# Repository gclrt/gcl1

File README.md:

Garbage Collection Module 1

Run compme.tcl from within Modelsim.

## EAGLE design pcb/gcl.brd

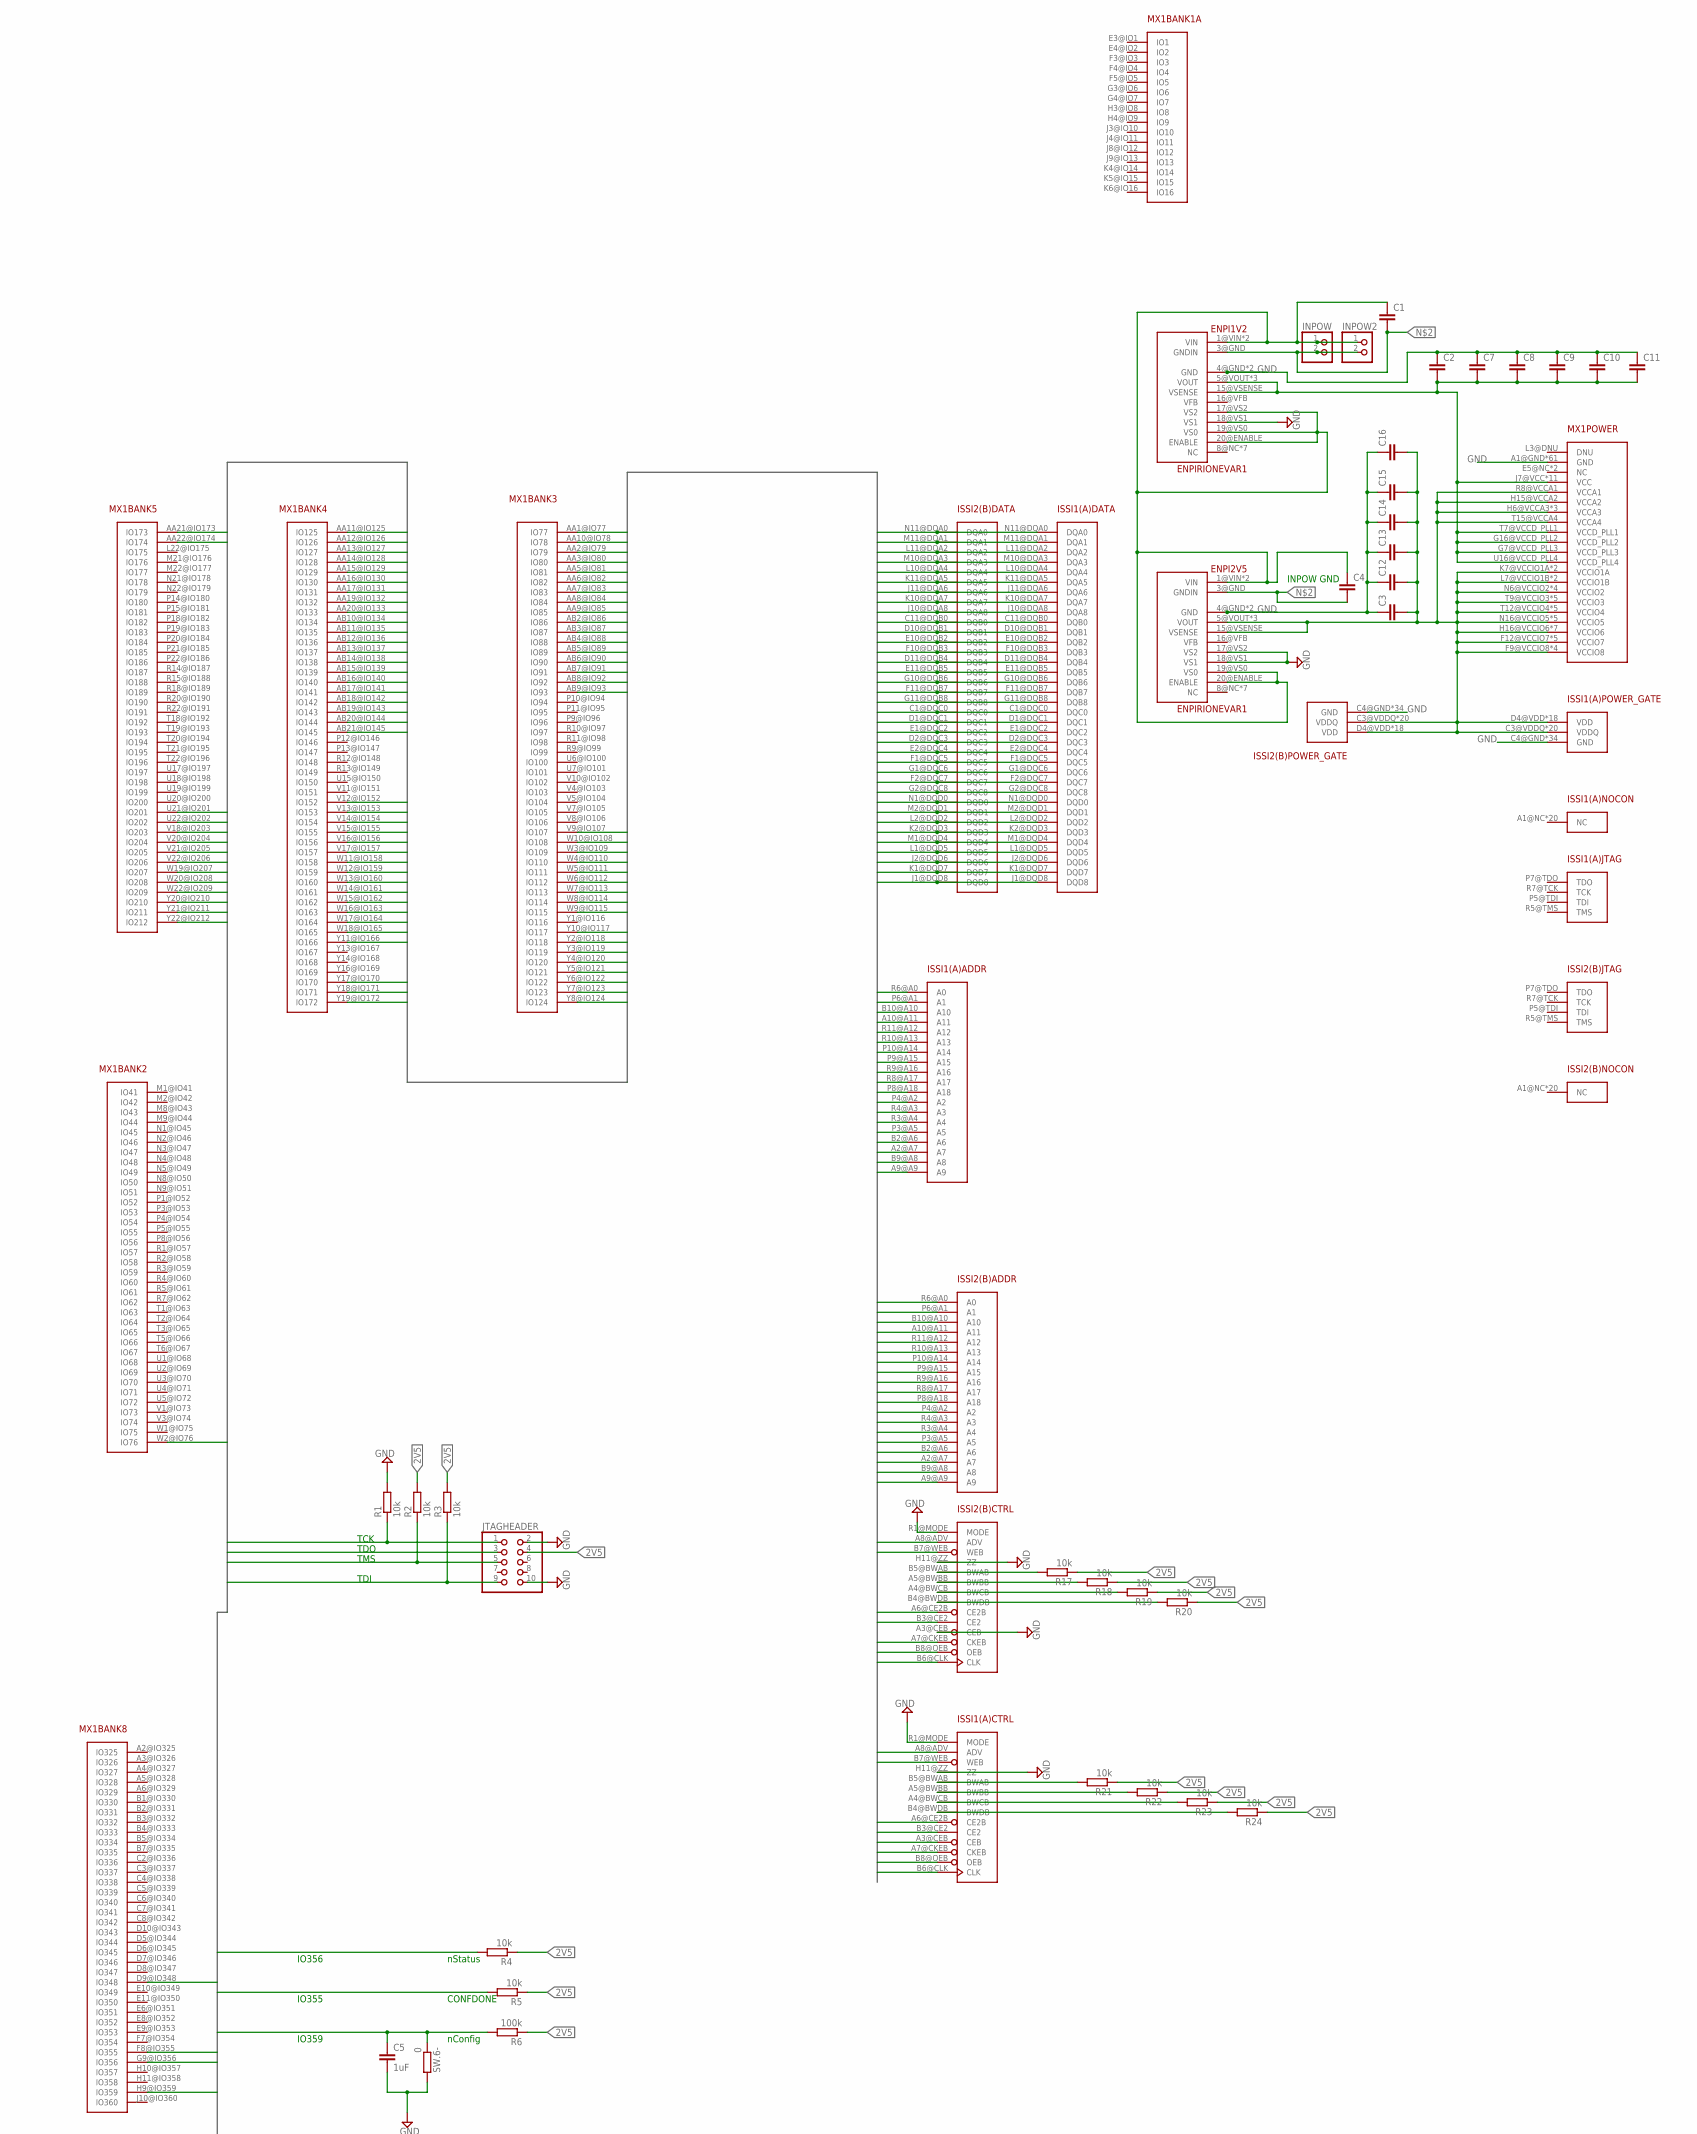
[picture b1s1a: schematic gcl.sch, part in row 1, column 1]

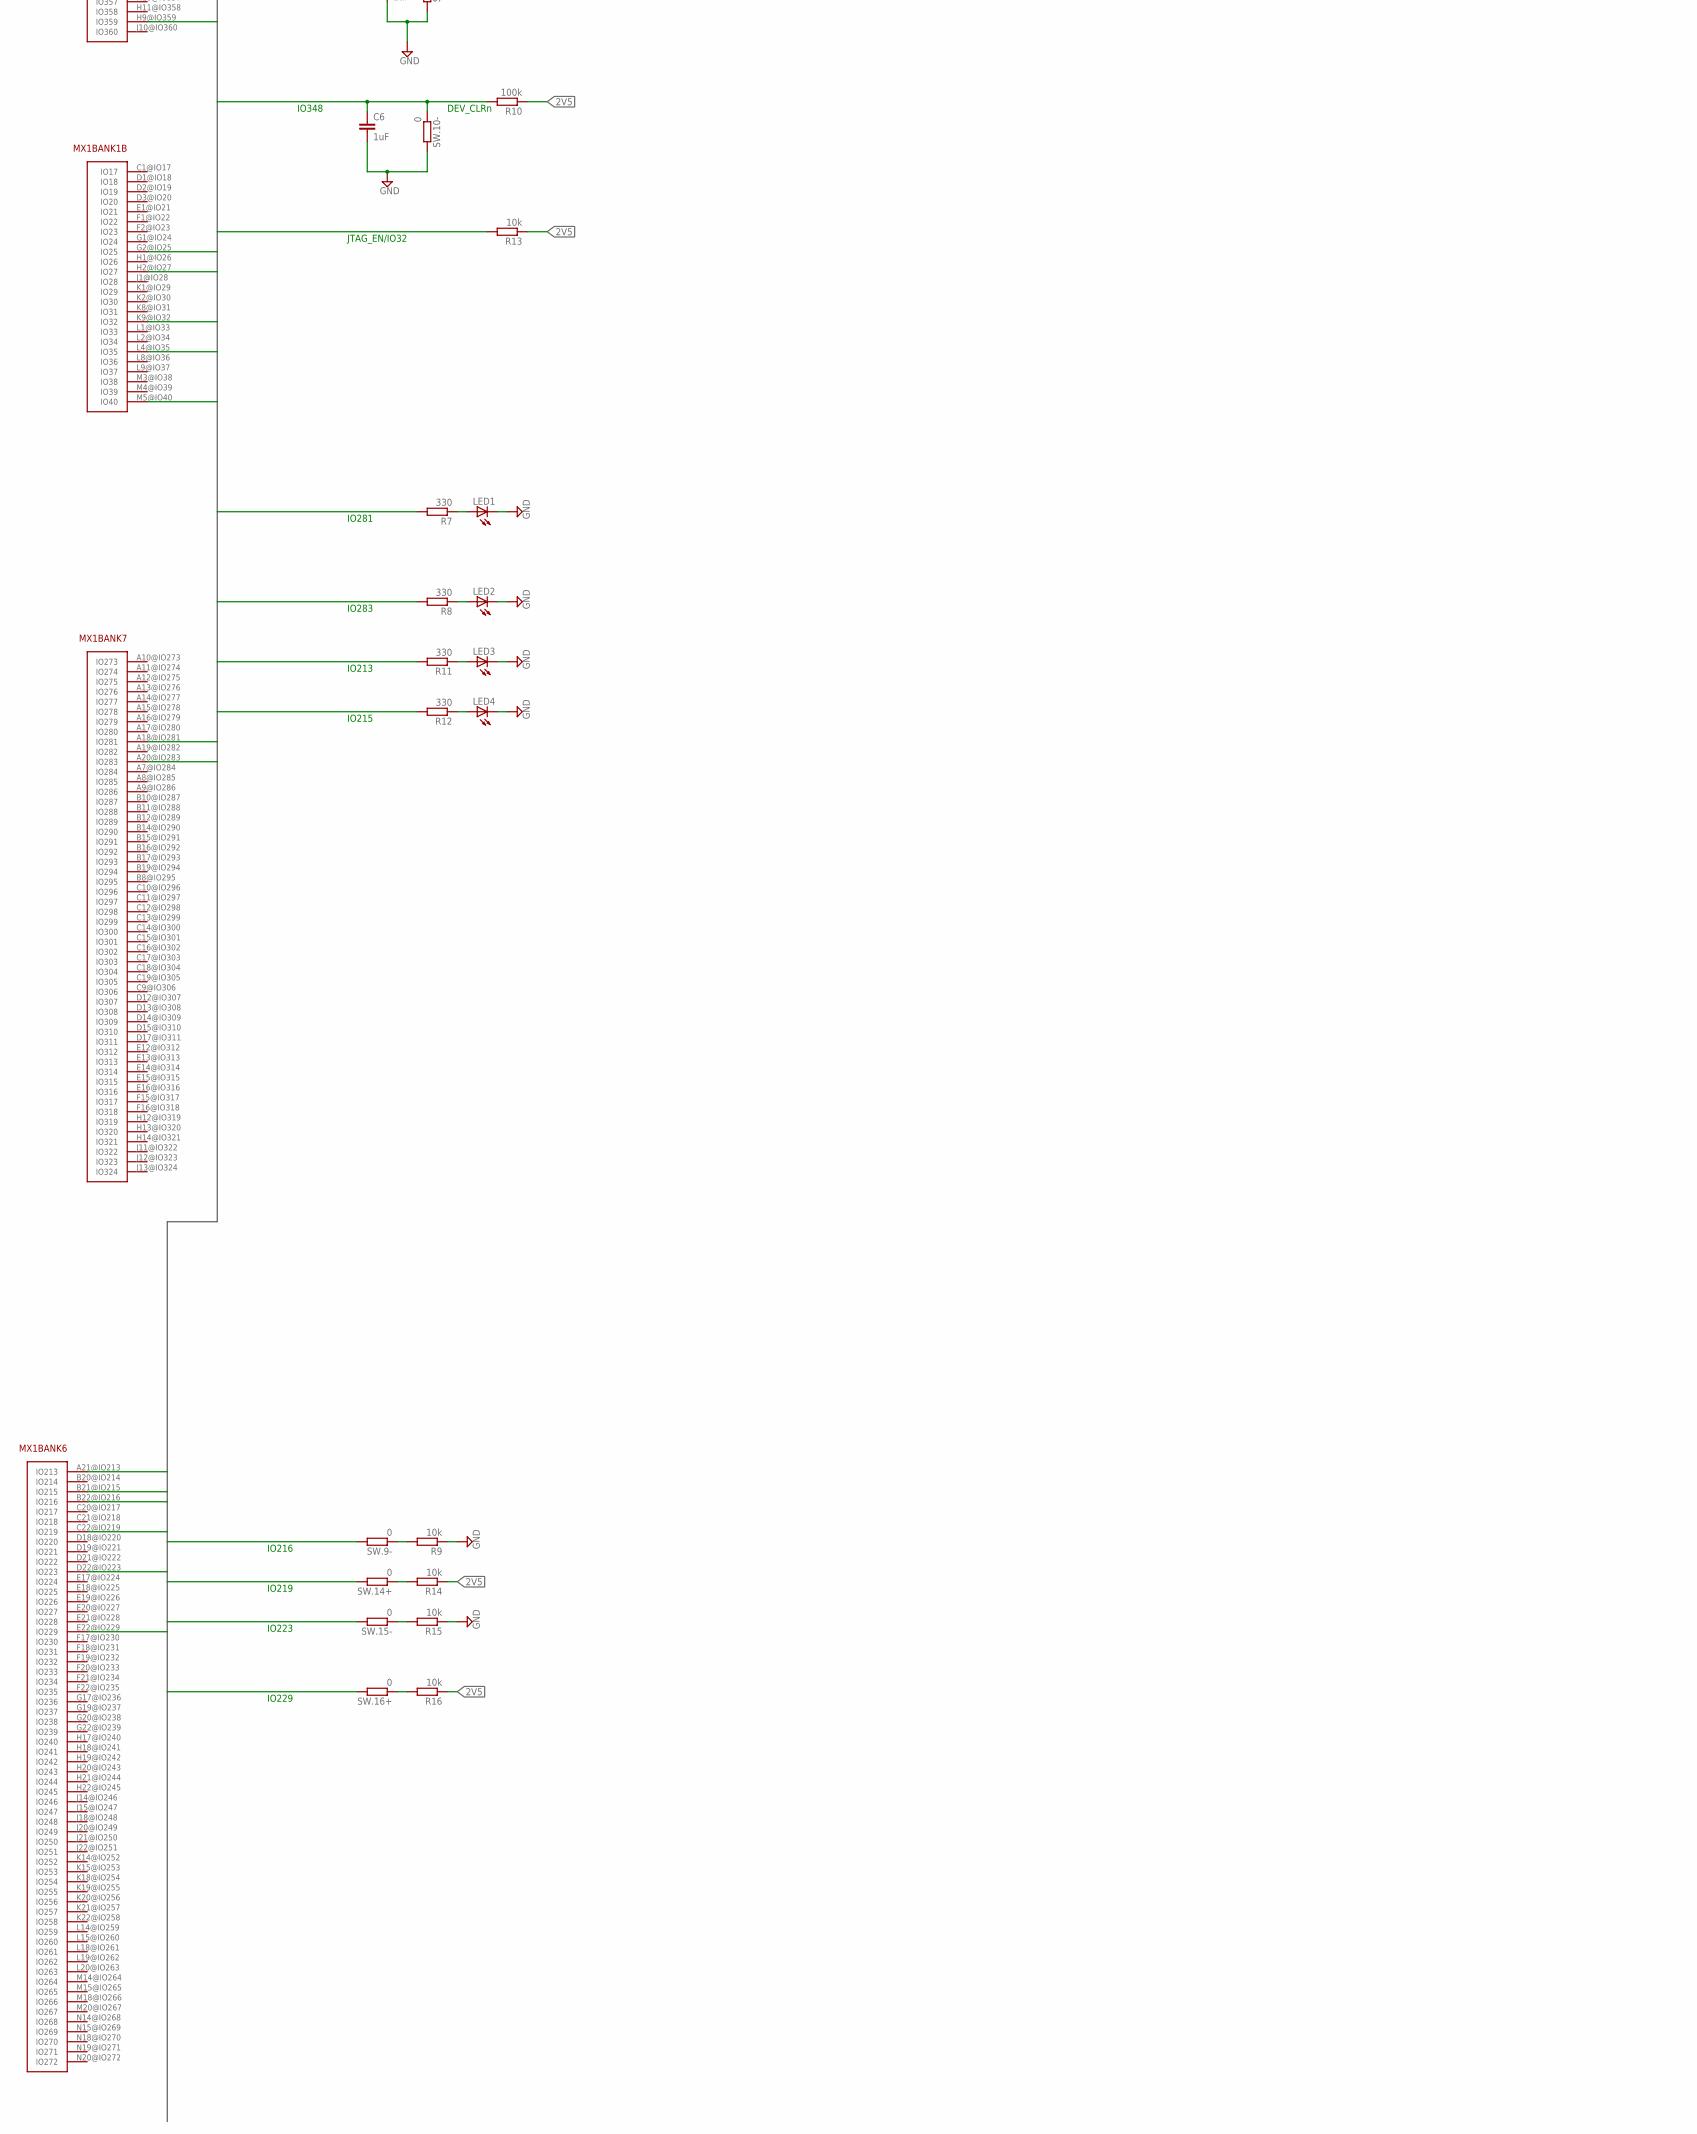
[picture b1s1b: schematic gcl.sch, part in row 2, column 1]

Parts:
C1, C2, C3, C4, C7, C8, C9, C10, C11, C12, C13, C14, C15, C16: C-EUC0805; C0805
C5, C6: 1uF; C0805
ENPI1V2, ENPI2V5: ENPIRIONEVAR1; EPAC
INPOW, INPOW2: PINHD-1X2; 1X02
ISSI1(A), ISSI2(B): ISSIDEVISSIVAR; ISSI
JTAGHEADER: PINHD-2X5; 2X05
LED1, LED2, LED3, LED4: LEDSML0805; SML0805
MX1: MXMXDEVICE; MXPAC
R1, R2, R3, R4, R5, R9, R13, R14, R15, R16, R17, R18, R19, R20, R21, R22, R23, R24: 10k; M0805
R6, R10: 100k; M0805
R7, R8, R11, R12: 330; M0805
SW.6-, SW.9-, SW.10-, SW.14+, SW.15-, SW.16+: 0; M0805

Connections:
1V2: C2.2, C7.2, C8.2, C9.2, C10.2, C11.2, ENPI1V2.5@VOUT (VOUT), ENPI1V2.6@VOUT (VOUT), ENPI1V2.7@VOUT (VOUT), ENPI1V2.15@VSENSE (VSENSE), MX1.G7@VCCD_PLL3 (VCCD_PLL3), MX1.G16@VCCD_PLL2 (VCCD_PLL2), MX1.J7@VCC (VCC), MX1.K11@VCC (VCC), MX1.K13@VCC (VCC), MX1.L10@VCC (VCC), MX1.L11@VCC (VCC), MX1.L12@VCC (VCC), MX1.M11@VCC (VCC), MX1.M12@VCC (VCC), MX1.M13@VCC (VCC), MX1.N10@VCC (VCC), MX1.N12@VCC (VCC), MX1.T7@VCCD_PLL1 (VCCD_PLL1), MX1.U16@VCCD_PLL4 (VCCD_PLL4)
2V5: C3.2, C12.2, C13.2, C14.2, C15.2, C16.2, ENPI2V5.5@VOUT (VOUT), ENPI2V5.6@VOUT (VOUT), ENPI2V5.7@VOUT (VOUT), ENPI2V5.15@VSENSE (VSENSE), ISSI1(A).C3@VDDQ (VDDQ), ISSI1(A).C9@VDDQ (VDDQ), ISSI1(A).D3@VDDQ (VDDQ), ISSI1(A).D4@VDD (VDD), ISSI1(A).D8@VDD (VDD), ISSI1(A).D9@VDDQ (VDDQ), ISSI1(A).E3@VDDQ (VDDQ), ISSI1(A).E4@VDD (VDD), ISSI1(A).E8@VDD (VDD), ISSI1(A).E9@VDDQ (VDDQ), ISSI1(A).F3@VDDQ (VDDQ), ISSI1(A).F4@VDD (VDD), ISSI1(A).F8@VDD (VDD), ISSI1(A).F9@VDDQ (VDDQ), ISSI1(A).G3@VDDQ (VDDQ), ISSI1(A).G4@VDD (VDD), ISSI1(A).G8@VDD (VDD), ISSI1(A).G9@VDDQ (VDDQ), ISSI1(A).H4@VDD (VDD), ISSI1(A).H8@VDD (VDD), ISSI1(A).J3@VDDQ (VDDQ), ISSI1(A).J4@VDD (VDD), ISSI1(A).J8@VDD (VDD), ISSI1(A).J9@VDDQ (VDDQ), ISSI1(A).K3@VDDQ (VDDQ), ISSI1(A).K4@VDD (VDD), ISSI1(A).K8@VDD (VDD), ISSI1(A).K9@VDDQ (VDDQ), ISSI1(A).L3@VDDQ (VDDQ), ISSI1(A).L4@VDD (VDD), ISSI1(A).L8@VDD (VDD), ISSI1(A).L9@VDDQ (VDDQ), ISSI1(A).M3@VDDQ (VDDQ), ISSI1(A).M4@VDD (VDD), ISSI1(A).M8@VDD (VDD), ISSI1(A).M9@VDDQ (VDDQ), ISSI1(A).N3@VDDQ (VDDQ), ISSI1(A).N9@VDDQ (VDDQ), ISSI2(B).C3@VDDQ (VDDQ), ISSI2(B).C9@VDDQ (VDDQ), ISSI2(B).D3@VDDQ (VDDQ), ISSI2(B).D4@VDD (VDD), ISSI2(B).D8@VDD (VDD), ISSI2(B).D9@VDDQ (VDDQ), ISSI2(B).E3@VDDQ (VDDQ), ISSI2(B).E4@VDD (VDD), ISSI2(B).E8@VDD (VDD), ISSI2(B).E9@VDDQ (VDDQ), ISSI2(B).F3@VDDQ (VDDQ), ISSI2(B).F4@VDD (VDD), ISSI2(B).F8@VDD (VDD), ISSI2(B).F9@VDDQ (VDDQ), ISSI2(B).G3@VDDQ (VDDQ), ISSI2(B).G4@VDD (VDD), ISSI2(B).G8@VDD (VDD), ISSI2(B).G9@VDDQ (VDDQ), ISSI2(B).H4@VDD (VDD), ISSI2(B).H8@VDD (VDD), ISSI2(B).J3@VDDQ (VDDQ), ISSI2(B).J4@VDD (VDD), ISSI2(B).J8@VDD (VDD), ISSI2(B).J9@VDDQ (VDDQ), ISSI2(B).K3@VDDQ (VDDQ), ISSI2(B).K4@VDD (VDD), ISSI2(B).K8@VDD (VDD), ISSI2(B).K9@VDDQ (VDDQ), ISSI2(B).L3@VDDQ (VDDQ), ISSI2(B).L4@VDD (VDD), ISSI2(B).L8@VDD (VDD), ISSI2(B).L9@VDDQ (VDDQ), ISSI2(B).M3@VDDQ (VDDQ), ISSI2(B).M4@VDD (VDD), ISSI2(B).M8@VDD (VDD), ISSI2(B).M9@VDDQ (VDDQ), ISSI2(B).N3@VDDQ (VDDQ), ISSI2(B).N9@VDDQ (VDDQ), JTAGHEADER.4, MX1.F9@VCCIO8 (VCCIO8), MX1.F11@VCCIO8 (VCCIO8), MX1.F12@VCCIO7 (VCCIO7), MX1.F14@VCCIO7 (VCCIO7), MX1.G10@VCCIO8 (VCCIO8), MX1.G11@VCCIO8 (VCCIO8), MX1.G12@VCCIO7 (VCCIO7), MX1.G13@VCCIO7 (VCCIO7), MX1.G14@VCCIO7 (VCCIO7), MX1.H6@VCCA3 (VCCA3), MX1.H7@VCCA3 (VCCA3), MX1.H8@VCCA3 (VCCA3), MX1.H15@VCCA2 (VCCA2), MX1.H16@VCCIO6 (VCCIO6), MX1.J17@VCCIO6 (VCCIO6), MX1.K7@VCCIO1A (VCCIO1A), MX1.K16@VCCIO6 (VCCIO6), MX1.K17@VCCIO6 (VCCIO6), MX1.L6@VCCIO1A (VCCIO1A), MX1.L7@VCCIO1B (VCCIO1B), MX1.L16@VCCIO6 (VCCIO6), MX1.M6@VCCIO1B (VCCIO1B), MX1.M17@VCCIO6 (VCCIO6), MX1.N6@VCCIO2 (VCCIO2), MX1.N7@VCCIO2 (VCCIO2), MX1.N16@VCCIO5 (VCCIO5), MX1.N17@VCCIO6 (VCCIO6), MX1.P7@VCCIO2 (VCCIO2), MX1.P16@VCCIO5 (VCCIO5), MX1.R6@VCCIO2 (VCCIO2), MX1.R8@VCCA1 (VCCA1), MX1.R16@VCCIO5 (VCCIO5), MX1.R17@VCCIO5 (VCCIO5), MX1.T9@VCCIO3 (VCCIO3), MX1.T10@VCCIO3 (VCCIO3), MX1.T11@VCCIO3 (VCCIO3), MX1.T12@VCCIO4 (VCCIO4), MX1.T13@VCCIO4 (VCCIO4), MX1.T15@VCCA4 (VCCA4), MX1.T17@VCCIO5 (VCCIO5), MX1.U8@VCCIO3 (VCCIO3), MX1.U9@VCCIO3 (VCCIO3), MX1.U11@VCCIO4 (VCCIO4), MX1.U12@VCCIO4 (VCCIO4), MX1.U14@VCCIO4 (VCCIO4), R2.2, R3.2, R4.1, R5.1, R6.1, R10.1, R13.1, R14.1, R16.1, R17.1, R18.1, R19.1, R20.1, R21.1, R22.1, R23.1, R24.1
GND: C2.1, C3.1, C5.2, C6.2, C7.1, C8.1, C9.1, C10.1, C11.1, C12.1, C13.1, C14.1, C15.1, C16.1, ENPI1V2.4@GND (GND), ENPI1V2.18@VS1 (VS1), ENPI1V2.21@GND (GND), ENPI2V5.4@GND (GND), ENPI2V5.17@VS2 (VS2), ENPI2V5.18@VS1 (VS1), ENPI2V5.21@GND (GND), ISSI1(A).C4@GND (GND), ISSI1(A).C5@GND (GND), ISSI1(A).C6@GND (GND), ISSI1(A).C7@GND (GND), ISSI1(A).C8@GND (GND), ISSI1(A).D5@GND (GND), ISSI1(A).D6@GND (GND), ISSI1(A).D7@GND (GND), ISSI1(A).E5@GND (GND), ISSI1(A).E6@GND (GND), ISSI1(A).E7@GND (GND), ISSI1(A).F5@GND (GND), ISSI1(A).F6@GND (GND), ISSI1(A).F7@GND (GND), ISSI1(A).G5@GND (GND), ISSI1(A).G6@GND (GND), ISSI1(A).G7@GND (GND), ISSI1(A).H5@GND (GND), ISSI1(A).H6@GND (GND), ISSI1(A).H7@GND (GND), ISSI1(A).H11@ZZ (ZZ), ISSI1(A).J5@GND (GND), ISSI1(A).J6@GND (GND), ISSI1(A).J7@GND (GND), ISSI1(A).K5@GND (GND), ISSI1(A).K6@GND (GND), ISSI1(A).K7@GND (GND), ISSI1(A).L5@GND (GND), ISSI1(A).L6@GND (GND), ISSI1(A).L7@GND (GND), ISSI1(A).M5@GND (GND), ISSI1(A).M6@GND (GND), ISSI1(A).M7@GND (GND), ISSI1(A).N4@GND (GND), ISSI1(A).N8@GND (GND), ISSI1(A).R1@MODE (MODE), ISSI2(B).A3@CEB (CEB), ISSI2(B).C4@GND (GND), ISSI2(B).C5@GND (GND), ISSI2(B).C6@GND (GND), ISSI2(B).C7@GND (GND), ISSI2(B).C8@GND (GND), ISSI2(B).D5@GND (GND), ISSI2(B).D6@GND (GND), ISSI2(B).D7@GND (GND), ISSI2(B).E5@GND (GND), ISSI2(B).E6@GND (GND), ISSI2(B).E7@GND (GND), ISSI2(B).F5@GND (GND), ISSI2(B).F6@GND (GND), ISSI2(B).F7@GND (GND), ISSI2(B).G5@GND (GND), ISSI2(B).G6@GND (GND), ISSI2(B).G7@GND (GND), ISSI2(B).H5@GND (GND), ISSI2(B).H6@GND (GND), ISSI2(B).H7@GND (GND), ISSI2(B).H11@ZZ (ZZ), ISSI2(B).J5@GND (GND), ISSI2(B).J6@GND (GND), ISSI2(B).J7@GND (GND), ISSI2(B).K5@GND (GND), ISSI2(B).K6@GND (GND), ISSI2(B).K7@GND (GND), ISSI2(B).L5@GND (GND), ISSI2(B).L6@GND (GND), ISSI2(B).L7@GND (GND), ISSI2(B).M5@GND (GND), ISSI2(B).M6@GND (GND), ISSI2(B).M7@GND (GND), ISSI2(B).N4@GND (GND), ISSI2(B).N8@GND (GND), ISSI2(B).R1@MODE (MODE), JTAGHEADER.2, JTAGHEADER.10, LED1.C, LED2.C, LED3.C, LED4.C, MX1.A1@GND (GND), MX1.A22@GND (GND), MX1.AA4@GND (GND), MX1.AA18@GND (GND), MX1.AB1@GND (GND), MX1.AB22@GND (GND), MX1.B6@GND (GND), MX1.B9@GND (GND), MX1.B13@GND (GND), MX1.B18@GND (GND), MX1.D4@GND (GND), MX1.D11@GND (GND), MX1.D16@GND (GND), MX1.D20@GND (GND), MX1.E2@GND (GND), MX1.E7@GND (GND), MX1.F10@GND (GND), MX1.F13@GND (GND), MX1.G5@GND (GND), MX1.G6@GND (GND), MX1.G8@GND (GND), MX1.G15@GND (GND), MX1.G18@GND (GND), MX1.G21@GND (GND), MX1.H5@GND (GND), MX1.J2@GND (GND), MX1.J5@GND (GND), MX1.J6@GND (GND), MX1.J16@GND (GND), MX1.J19@GND (GND), MX1.K3@GND (GND), MX1.K10@GND (GND), MX1.K12@GND (GND), MX1.L5@GND (GND), MX1.L13@GND (GND), MX1.L17@GND (GND), MX1.L21@GND (GND), MX1.M7@GND (GND), MX1.M10@GND (GND), MX1.M16@GND (GND), MX1.M19@GND (GND), MX1.N11@GND (GND), MX1.N13@GND (GND), MX1.P2@GND (GND), MX1.P6@GND (GND), MX1.P17@GND (GND), MX1.R19@GND (GND), MX1.R21@GND (GND), MX1.T4@GND (GND), MX1.T8@GND (GND), MX1.T14@GND (GND), MX1.T16@GND (GND), MX1.U10@GND (GND), MX1.U13@GND (GND), MX1.V2@GND (GND), MX1.V6@GND (GND), MX1.V19@GND (GND), MX1.W21@GND (GND), MX1.Y9@GND (GND), MX1.Y12@GND (GND), MX1.Y15@GND (GND), R1.2, R9.1, R15.1, SW.6-.2, SW.10-.2
IO25: JTAGHEADER.1, MX1.G2@IO25 (IO25), R1.1
IO27: JTAGHEADER.5, MX1.H2@IO27 (IO27), R2.1
IO32: MX1.K9@IO32 (IO32), R13.2
IO35: JTAGHEADER.9, MX1.L4@IO35 (IO35), R3.1
IO40: JTAGHEADER.3, MX1.M5@IO40 (IO40)
IO76: ISSI2(B).A7@CKEB (CKEB), MX1.W2@IO76 (IO76)
IO77: ISSI2(B).B7@WEB (WEB), MX1.AA1@IO77 (IO77)
IO78: ISSI1(A).E2@DQC4 (DQC4), ISSI2(B).E2@DQC4 (DQC4), MX1.AA10@IO78 (IO78)
IO79: ISSI1(A).A3@CEB (CEB), MX1.AA2@IO79 (IO79)
IO80: ISSI1(A).A10@A11 (A11), MX1.AA3@IO80 (IO80)
IO81: ISSI1(A).B2@A6 (A6), MX1.AA5@IO81 (IO81)
IO82: ISSI1(A).B8@OEB (OEB), MX1.AA6@IO82 (IO82)
IO83: ISSI2(B).B10@A10 (A10), MX1.AA7@IO83 (IO83)
IO84: ISSI2(B).B2@A6 (A6), MX1.AA8@IO84 (IO84)
IO85: ISSI1(A).D2@DQC3 (DQC3), ISSI2(B).D2@DQC3 (DQC3), MX1.AA9@IO85 (IO85)
IO86: ISSI1(A).A2@A7 (A7), MX1.AB2@IO86 (IO86)
IO87: ISSI1(A).A7@CKEB (CKEB), MX1.AB3@IO87 (IO87)
IO88: ISSI2(B).B8@OEB (OEB), MX1.AB4@IO88 (IO88)
IO89: ISSI1(A).A6@CE2B (CE2B), MX1.AB5@IO89 (IO89)
IO90: ISSI1(A).B7@WEB (WEB), MX1.AB6@IO90 (IO90)
IO91: ISSI2(B).A10@A11 (A11), MX1.AB7@IO91 (IO91)
IO92: ISSI1(A).C1@DQC0 (DQC0), ISSI2(B).C1@DQC0 (DQC0), MX1.AB8@IO92 (IO92)
IO93: ISSI1(A).D1@DQC1 (DQC1), ISSI2(B).D1@DQC1 (DQC1), MX1.AB9@IO93 (IO93)
IO107: ISSI1(A).D11@DQB4 (DQB4), ISSI2(B).D11@DQB4 (DQB4), MX1.V9@IO107 (IO107)
IO108: ISSI1(A).E11@DQB5 (DQB5), ISSI2(B).E11@DQB5 (DQB5), MX1.W10@IO108 (IO108)
IO109: ISSI1(A).A8@ADV (ADV), MX1.W3@IO109 (IO109)
IO110: ISSI2(B).A6@CE2B (CE2B), MX1.W4@IO110 (IO110)
IO111: ISSI1(A).B6@CLK (CLK), ISSI2(B).B6@CLK (CLK), MX1.W5@IO111 (IO111)
IO112: ISSI1(A).B10@A10 (A10), MX1.W6@IO112 (IO112)
IO113: ISSI2(B).B9@A8 (A8), MX1.W7@IO113 (IO113)
IO114: ISSI1(A).C11@DQB0 (DQB0), ISSI2(B).C11@DQB0 (DQB0), MX1.W8@IO114 (IO114)
IO115: ISSI1(A).D10@DQB1 (DQB1), ISSI2(B).D10@DQB1 (DQB1), MX1.W9@IO115 (IO115)
IO117: ISSI1(A).E10@DQB2 (DQB2), ISSI2(B).E10@DQB2 (DQB2), MX1.Y10@IO117 (IO117)
IO118: ISSI2(B).A8@ADV (ADV), MX1.Y2@IO118 (IO118)
IO119: ISSI1(A).A9@A9 (A9), MX1.Y3@IO119 (IO119)
IO120: ISSI2(B).B3@CE2 (CE2), MX1.Y4@IO120 (IO120)
IO121: ISSI1(A).B3@CE2 (CE2), MX1.Y5@IO121 (IO121)
IO122: ISSI1(A).B9@A8 (A8), MX1.Y6@IO122 (IO122)
IO123: ISSI2(B).A9@A9 (A9), MX1.Y7@IO123 (IO123)
IO124: ISSI2(B).A2@A7 (A7), MX1.Y8@IO124 (IO124)
IO125: ISSI1(A).F2@DQC7 (DQC7), ISSI2(B).F2@DQC7 (DQC7), MX1.AA11@IO125 (IO125)
IO126: ISSI1(A).G2@DQC8 (DQC8), ISSI2(B).G2@DQC8 (DQC8), MX1.AA12@IO126 (IO126)
IO127: ISSI1(A).J2@DQD6 (DQD6), ISSI2(B).J2@DQD6 (DQD6), MX1.AA13@IO127 (IO127)
IO128: ISSI1(A).K2@DQD3 (DQD3), ISSI2(B).K2@DQD3 (DQD3), MX1.AA14@IO128 (IO128)
IO129: ISSI1(A).L2@DQD2 (DQD2), ISSI2(B).L2@DQD2 (DQD2), MX1.AA15@IO129 (IO129)
IO130: ISSI1(A).M2@DQD1 (DQD1), ISSI2(B).M2@DQD1 (DQD1), MX1.AA16@IO130 (IO130)
IO131: ISSI2(B).P3@A5 (A5), MX1.AA17@IO131 (IO131)
IO132: ISSI2(B).R10@A13 (A13), MX1.AA19@IO132 (IO132)
IO133: ISSI2(B).R9@A16 (A16), MX1.AA20@IO133 (IO133)
IO134: ISSI1(A).E1@DQC2 (DQC2), ISSI2(B).E1@DQC2 (DQC2), MX1.AB10@IO134 (IO134)
IO135: ISSI1(A).F1@DQC5 (DQC5), ISSI2(B).F1@DQC5 (DQC5), MX1.AB11@IO135 (IO135)
IO136: ISSI1(A).G1@DQC6 (DQC6), ISSI2(B).G1@DQC6 (DQC6), MX1.AB12@IO136 (IO136)
IO137: ISSI1(A).J1@DQD8 (DQD8), ISSI2(B).J1@DQD8 (DQD8), MX1.AB13@IO137 (IO137)
IO138: ISSI1(A).K1@DQD7 (DQD7), ISSI2(B).K1@DQD7 (DQD7), MX1.AB14@IO138 (IO138)
IO139: ISSI1(A).L1@DQD5 (DQD5), ISSI2(B).L1@DQD5 (DQD5), MX1.AB15@IO139 (IO139)
IO140: ISSI1(A).M1@DQD4 (DQD4), ISSI2(B).M1@DQD4 (DQD4), MX1.AB16@IO140 (IO140)
IO141: ISSI1(A).N1@DQD0 (DQD0), ISSI2(B).N1@DQD0 (DQD0), MX1.AB17@IO141 (IO141)
IO142: ISSI2(B).R4@A3 (A3), MX1.AB18@IO142 (IO142)
IO143: ISSI2(B).R11@A12 (A12), MX1.AB19@IO143 (IO143)
IO144: ISSI2(B).R8@A17 (A17), MX1.AB20@IO144 (IO144)
IO145: ISSI1(A).P10@A14 (A14), MX1.AB21@IO145 (IO145)
IO152: ISSI1(A).G11@DQB8 (DQB8), ISSI2(B).G11@DQB8 (DQB8), MX1.V12@IO152 (IO152)
IO153: ISSI1(A).J11@DQA6 (DQA6), ISSI2(B).J11@DQA6 (DQA6), MX1.V13@IO153 (IO153)
IO154: ISSI1(A).K11@DQA5 (DQA5), ISSI2(B).K11@DQA5 (DQA5), MX1.V14@IO154 (IO154)
IO155: ISSI1(A).L11@DQA2 (DQA2), ISSI2(B).L11@DQA2 (DQA2), MX1.V15@IO155 (IO155)
IO156: ISSI1(A).M11@DQA1 (DQA1), ISSI2(B).M11@DQA1 (DQA1), MX1.V16@IO156 (IO156)
IO157: ISSI1(A).N11@DQA0 (DQA0), ISSI2(B).N11@DQA0 (DQA0), MX1.V17@IO157 (IO157)
IO158: ISSI1(A).F11@DQB7 (DQB7), ISSI2(B).F11@DQB7 (DQB7), MX1.W11@IO158 (IO158)
IO159: ISSI1(A).G10@DQB6 (DQB6), ISSI2(B).G10@DQB6 (DQB6), MX1.W12@IO159 (IO159)
IO160: ISSI1(A).J10@DQA8 (DQA8), ISSI2(B).J10@DQA8 (DQA8), MX1.W13@IO160 (IO160)
IO161: ISSI1(A).K10@DQA7 (DQA7), ISSI2(B).K10@DQA7 (DQA7), MX1.W14@IO161 (IO161)
IO162: ISSI1(A).L10@DQA4 (DQA4), ISSI2(B).L10@DQA4 (DQA4), MX1.W15@IO162 (IO162)
IO163: ISSI1(A).M10@DQA3 (DQA3), ISSI2(B).M10@DQA3 (DQA3), MX1.W16@IO163 (IO163)
IO164: ISSI2(B).R3@A4 (A4), MX1.W17@IO164 (IO164)
IO165: ISSI2(B).R6@A0 (A0), MX1.W18@IO165 (IO165)
IO166: ISSI1(A).F10@DQB3 (DQB3), ISSI2(B).F10@DQB3 (DQB3), MX1.Y11@IO166 (IO166)
IO170: ISSI2(B).P4@A2 (A2), MX1.Y17@IO170 (IO170)
IO171: ISSI2(B).P6@A1 (A1), MX1.Y18@IO171 (IO171)
IO172: ISSI2(B).P9@A15 (A15), MX1.Y19@IO172 (IO172)
IO173: ISSI1(A).R11@A12 (A12), MX1.AA21@IO173 (IO173)
IO174: ISSI1(A).P6@A1 (A1), MX1.AA22@IO174 (IO174)
IO201: ISSI1(A).P3@A5 (A5), MX1.U21@IO201 (IO201)
IO202: ISSI1(A).R3@A4 (A4), MX1.U22@IO202 (IO202)
IO203: ISSI2(B).P8@A18 (A18), MX1.V18@IO203 (IO203)
IO204: ISSI1(A).P8@A18 (A18), MX1.V20@IO204 (IO204)
IO205: ISSI1(A).R8@A17 (A17), MX1.V21@IO205 (IO205)
IO206: ISSI1(A).P4@A2 (A2), MX1.V22@IO206 (IO206)
IO207: ISSI2(B).P10@A14 (A14), MX1.W19@IO207 (IO207)
IO208: ISSI1(A).R9@A16 (A16), MX1.W20@IO208 (IO208)
IO209: ISSI1(A).R4@A3 (A3), MX1.W22@IO209 (IO209)
IO210: ISSI1(A).R10@A13 (A13), MX1.Y20@IO210 (IO210)
IO211: ISSI1(A).P9@A15 (A15), MX1.Y21@IO211 (IO211)
IO212: ISSI1(A).R6@A0 (A0), MX1.Y22@IO212 (IO212)
IO213: MX1.A21@IO213 (IO213), R11.2
IO215: MX1.B21@IO215 (IO215), R12.2
IO216: MX1.B22@IO216 (IO216), SW.9-.2
IO219: MX1.C22@IO219 (IO219), SW.14+.2
IO223: MX1.D22@IO223 (IO223), SW.15-.2
IO229: MX1.E22@IO229 (IO229), SW.16+.2
IO281: MX1.A18@IO281 (IO281), R7.2
IO283: MX1.A20@IO283 (IO283), R8.2
IO348: C6.1, MX1.D9@IO348 (IO348), R10.2, SW.10-.1
IO355: MX1.F8@IO355 (IO355), R5.2
IO356: MX1.G9@IO356 (IO356), R4.2
IO359: C5.1, MX1.H9@IO359 (IO359), R6.2, SW.6-.1
unnamed: LED1.A, R7.1
unnamed: C1.2, C4.2, ENPI1V2.3@GND (GNDIN), ENPI2V5.3@GND (GNDIN), INPOW.2, INPOW2.2
unnamed: LED3.A, R11.1
unnamed: LED2.A, R8.1
unnamed: R9.2, SW.9-.1
unnamed: LED4.A, R12.1
unnamed: R14.2, SW.14+.1
unnamed: ISSI2(B).B5@BWAB (BWAB), R17.2
unnamed: R16.2, SW.16+.1
unnamed: R15.2, SW.15-.1
unnamed: ISSI1(A).B5@BWAB (BWAB), R21.2
unnamed: ISSI2(B).A5@BWBB (BWBB), R18.2
unnamed: ISSI2(B).A4@BWCB (BWCB), R19.2
unnamed: ISSI1(A).A5@BWBB (BWBB), R22.2
unnamed: ISSI1(A).B4@BWDB (BWDB), R24.2
unnamed: ISSI2(B).B4@BWDB (BWDB), R20.2
unnamed: ISSI1(A).A4@BWCB (BWCB), R23.2
VIN: C1.1, C4.1, ENPI1V2.1@VIN (VIN), ENPI1V2.2@VIN (VIN), ENPI1V2.17@VS2 (VS2), ENPI1V2.19@VS0 (VS0), ENPI1V2.20@ENABLE (ENABLE), ENPI2V5.1@VIN (VIN), ENPI2V5.2@VIN (VIN), ENPI2V5.19@VS0 (VS0), ENPI2V5.20@ENABLE (ENABLE), INPOW.1, INPOW2.1

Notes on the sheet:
TDI
TMS
TDO
TCK
nStatus
CONFDONE
nConfig
IO283
IO281
IO216
IO219
INPOW GND
DEV_CLRn
IO213
IO215
IO348
IO359
IO355
IO356
JTAG_EN/IO32
IO229
IO223

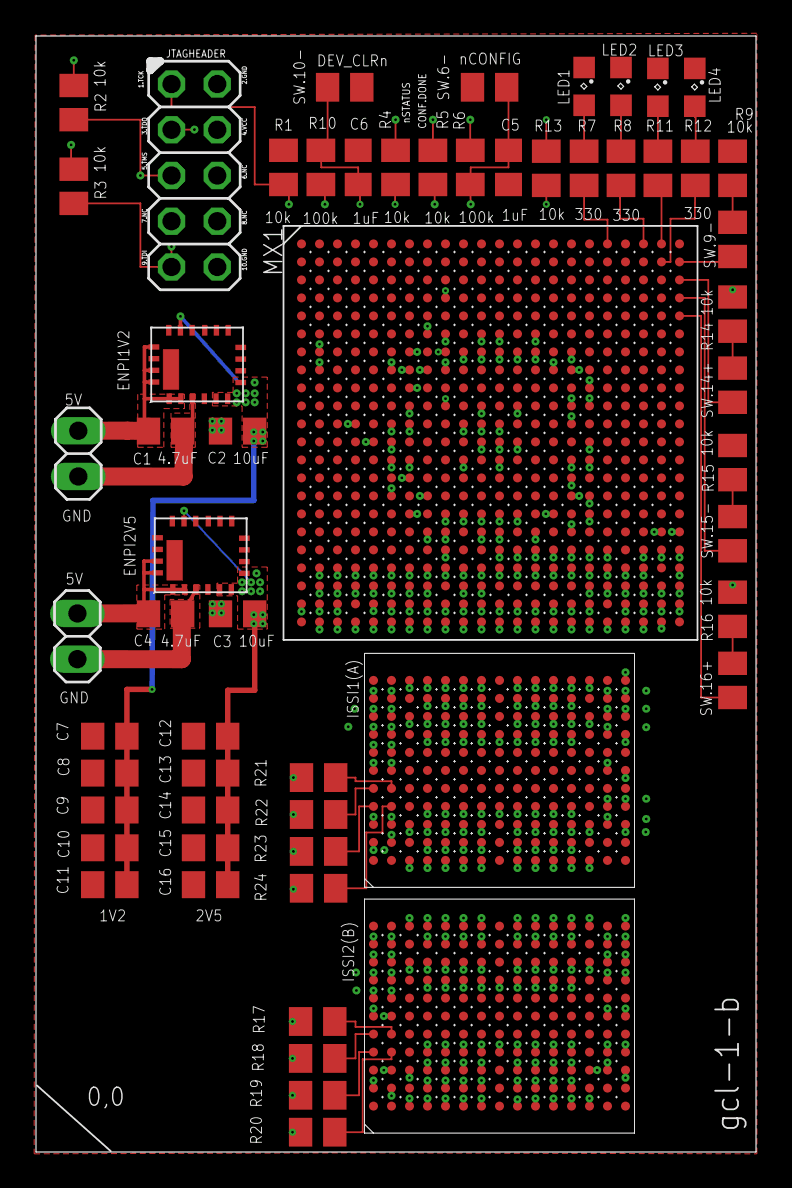
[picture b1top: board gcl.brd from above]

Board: 6 copper layers, 40.0 x 62.0 mm, 58 parts (0 on the bottom side), 126 nets.

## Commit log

2017-02-02 Initial gcl-1 commit
    Some extra files will be removed as needed.
2017-02-03 gcl-1-b pcb
    Eagle schematics, board, and dru for Eurocircuit.
2017-02-03 HDL files directory
2017-02-06 Modelsim
    Worked using Modelsim on an object reference table
2017-02-08 Benchmarks
2017-03-21 gcl1: updated readme to mention EDA Playground

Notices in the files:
pcb/gcl.brd:
Copyright: 2017, Copenhagen Business School, Dept. IT Mgt.
License: Simplified BSD License
